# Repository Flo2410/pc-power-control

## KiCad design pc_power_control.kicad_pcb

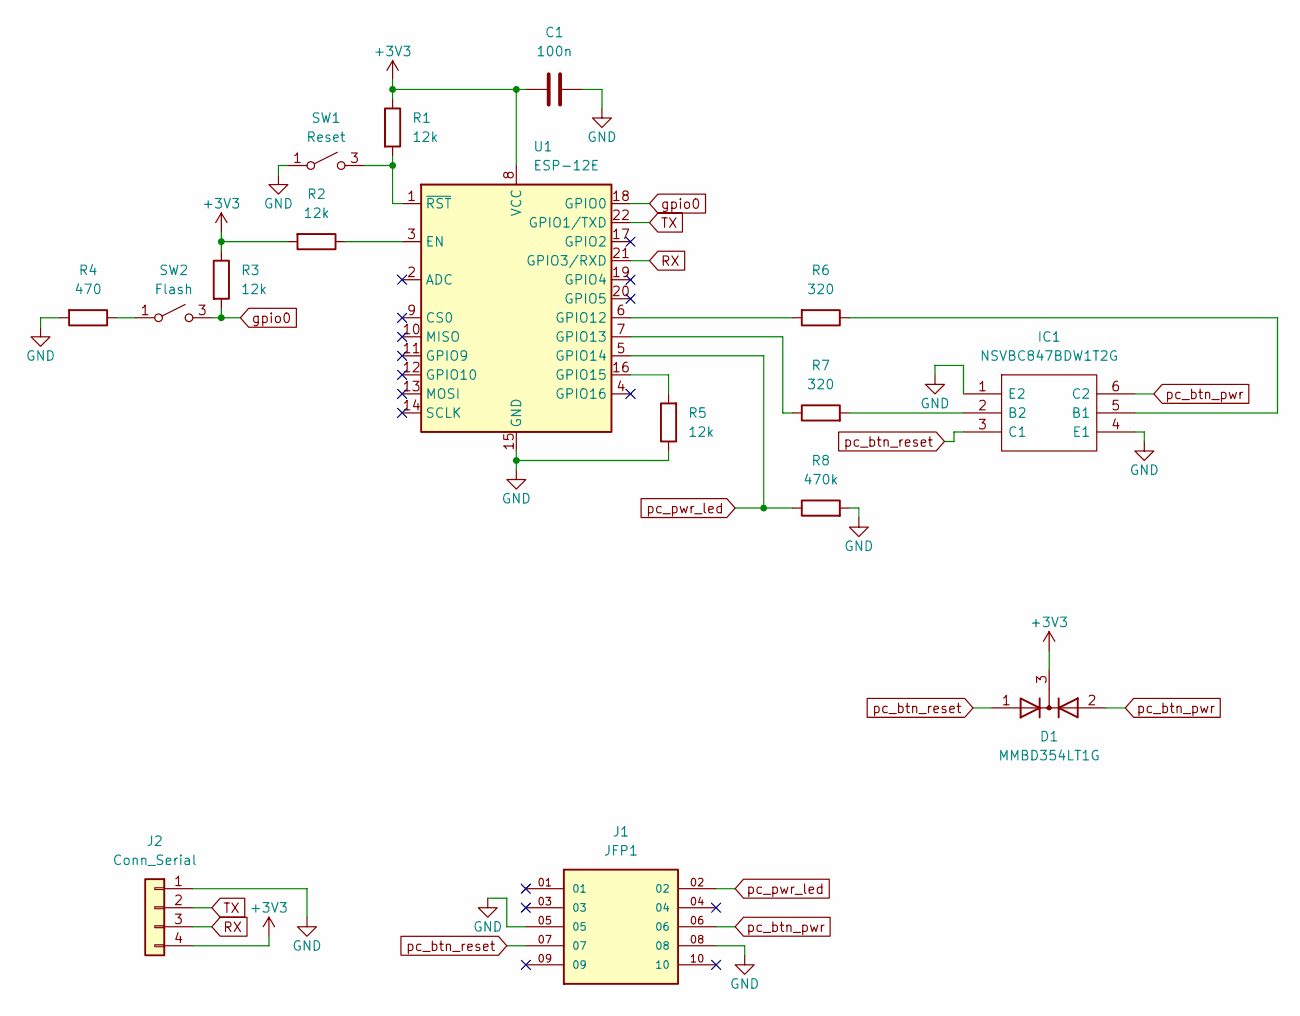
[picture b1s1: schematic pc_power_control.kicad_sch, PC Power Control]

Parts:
C1: 100n; C_0805_2012Metric_Pad1.18x1.45mm_HandSolder
D1: MMBD354LT1G; SOT-23; Mouser Part Number 863-MMBD354LT1G
IC1: NSVBC847BDW1T2G; SOT65P210X110-6N; Mouser Part Number 863-NSVBC847BDW1T2G
J1: JFP1; SAMTEC_SSQ-105-04-F-D; PARTREV R
J2: Conn_Serial; PinHeader_1x04_P1.27mm_Vertical
R1, R2, R3, R5: 12k; R_0805_2012Metric_Pad1.20x1.40mm_HandSolder
R4: 470; R_0805_2012Metric_Pad1.20x1.40mm_HandSolder
R6, R7: 320; R_0805_2012Metric_Pad1.20x1.40mm_HandSolder
R8: 470k; R_0805_2012Metric_Pad1.20x1.40mm_HandSolder
SW1: Reset; RKC2SJF170SMTRLFS
SW2: Flash; RKC2SJF170SMTRLFS
U1: ESP-12E

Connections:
+3V3: C1.1, D1.3 (K), J2.4, R1.1, R2.2, R3.1, U1.8 (VCC)
GND: C1.2, IC1.1 (E2), IC1.4 (E1), J1.05, J1.08, J2.1, R4.2, R5.1, R8.2, SW1.1 (A), U1.15 (GND)
unnamed: IC1.5 (B1), R6.1
unnamed: IC1.2 (B2), R7.2
unnamed: R1.2, SW1.3 (B), U1.1 (~RST)
unnamed: R4.1, SW2.1 (A)
unnamed: R2.1, U1.3 (EN)
unnamed: R6.2, U1.6 (GPIO12)
unnamed: R7.1, U1.7 (GPIO13)
unnamed: R5.2, U1.16 (GPIO15)
RX: J2.3, U1.21 (GPIO3/RXD)
TX: J2.2, U1.22 (GPIO1/TXD)
gpio0: R3.2, SW2.3 (B), U1.18 (GPIO0)
pc_btn_pwr: D1.2 (A), IC1.6 (C2), J1.06
pc_btn_reset: D1.1 (A), IC1.3 (C1), J1.07
pc_pwr_led: J1.02, R8.1, U1.5 (GPIO14)

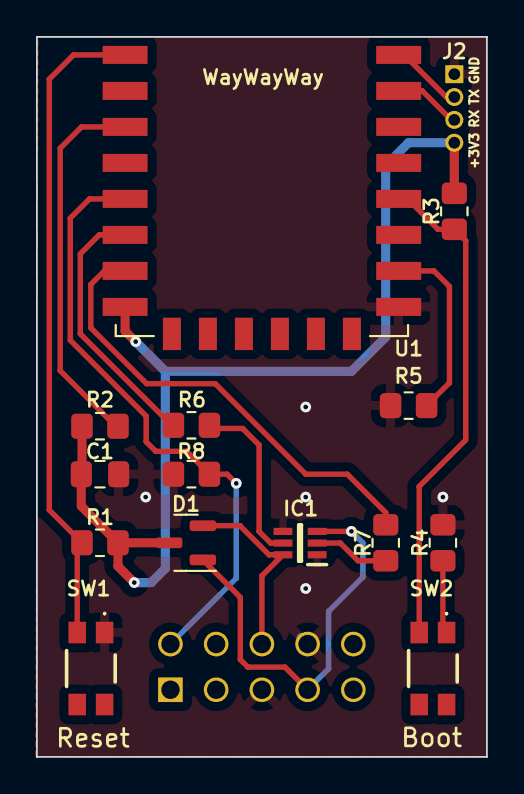
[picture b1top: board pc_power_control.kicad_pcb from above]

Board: 2 copper layers, 25.0 x 40.0 mm, 16 parts (1 on the bottom side), 16 nets.

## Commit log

2023-10-31 init git with v1.2
2023-10-31 Create LICENSE
2023-10-31 fixed button pin assignment
